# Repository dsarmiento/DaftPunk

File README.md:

# DaftPunk

##DaftController
DaftController will be the application that'll allow us to control our LED helmets via Bluetooth

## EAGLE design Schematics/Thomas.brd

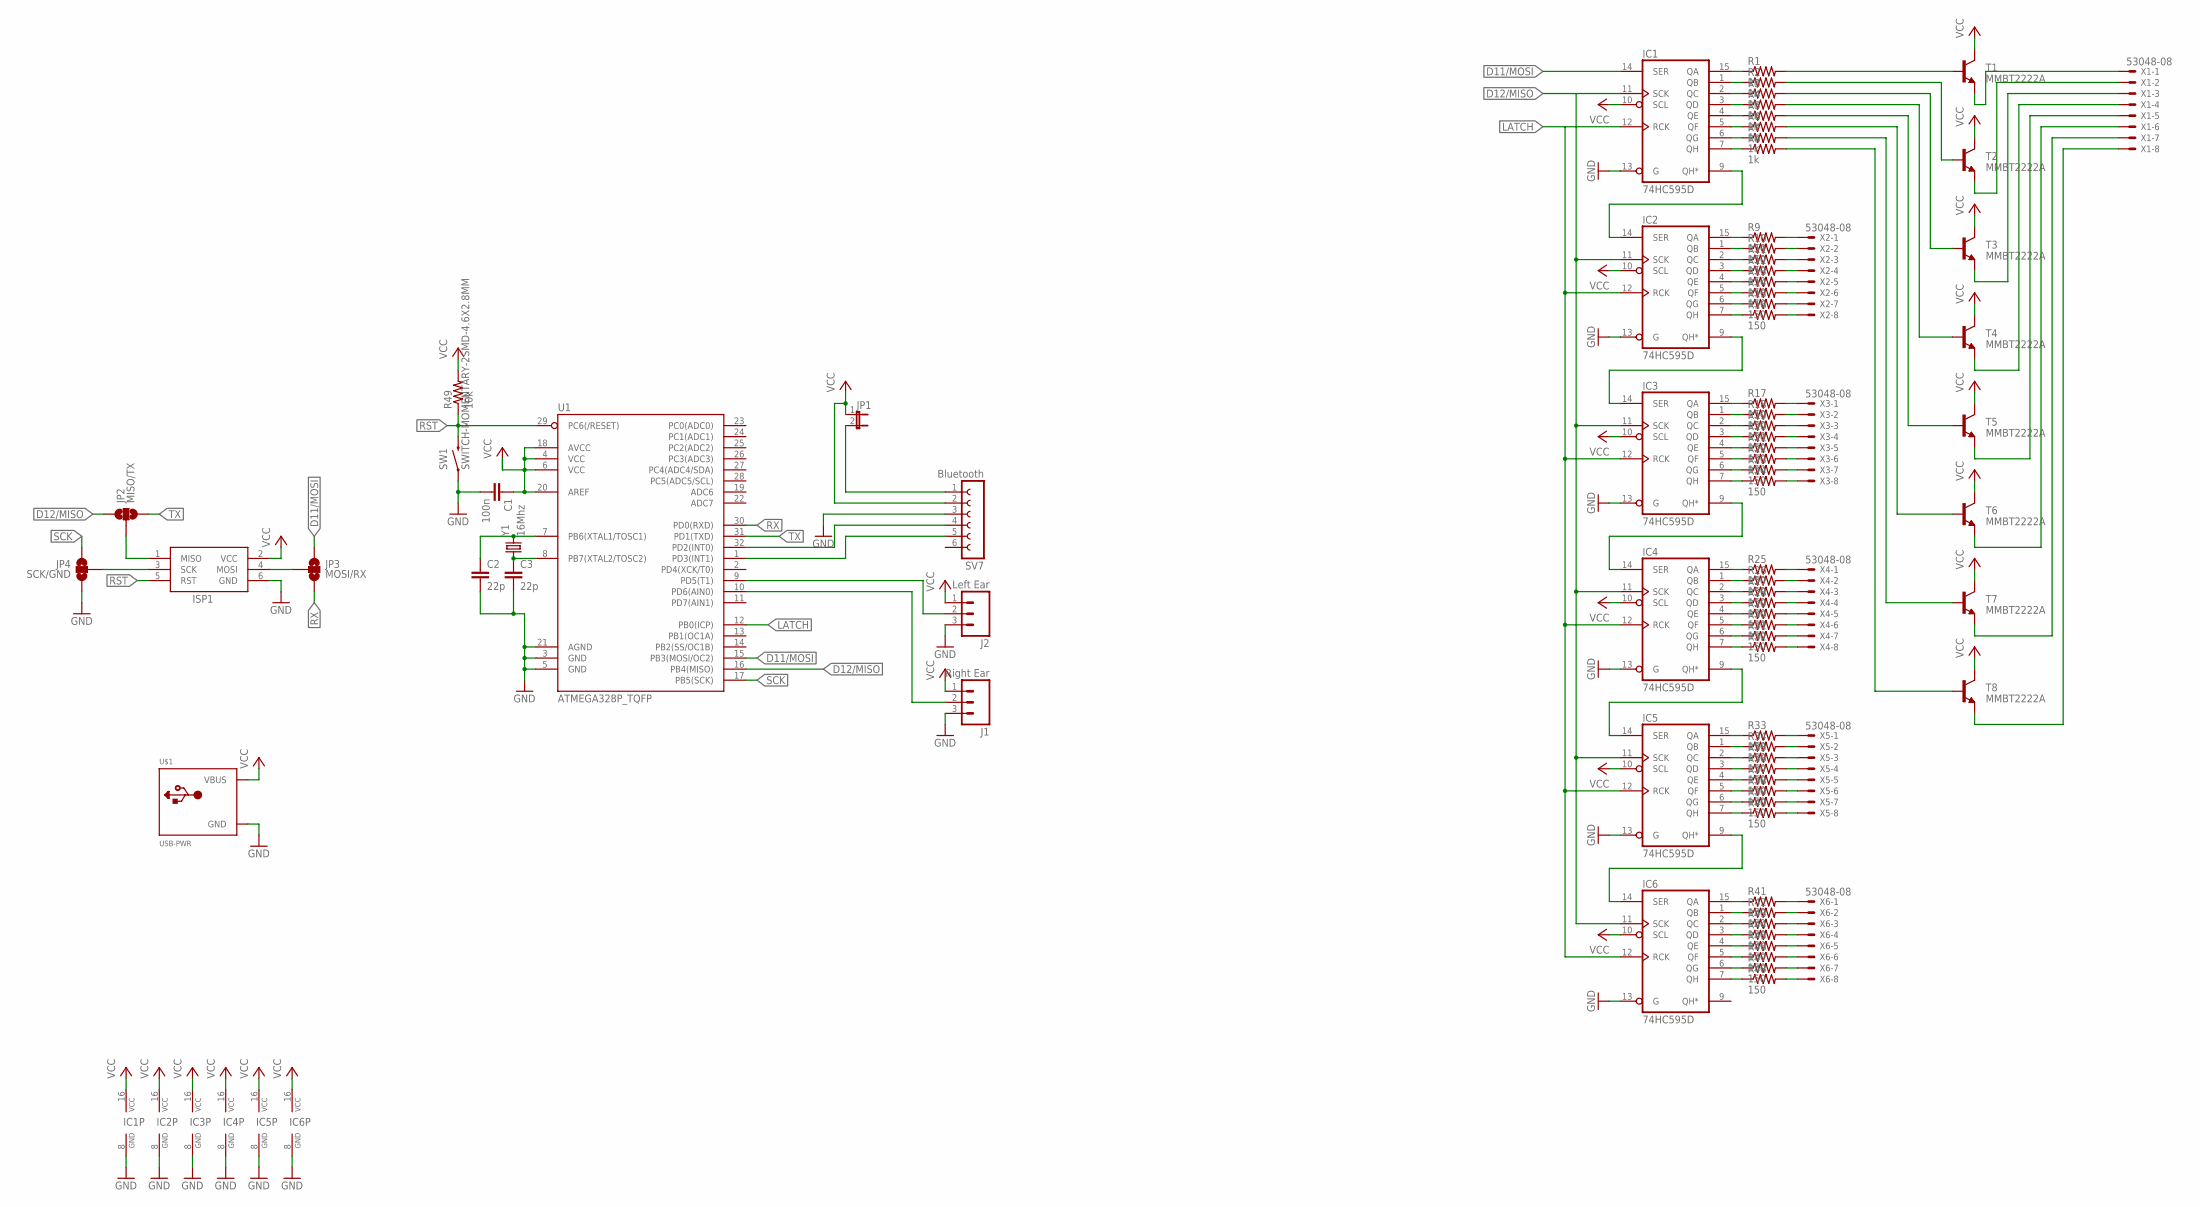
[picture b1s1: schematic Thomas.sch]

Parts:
C1: 100n; C0805K
C2, C3: 22p; C0805K
IC1, IC2, IC3, IC4, IC5, IC6: 74HC595D; SO16
ISP1: AVRISP-6; AVRISP
J1: Right Ear; 1X03
J2: Left Ear; 1X03
JP1: JUMPER-2SMD-NC; SJ_2S
JP2: MISO/TX; PAD-JUMPER-3-NO_YES_SILK
JP3: MOSI/RX; PAD-JUMPER-3-NO_YES_SILK
JP4: SCK/GND; PAD-JUMPER-3-NO_YES_SILK
R1, R2, R3, R4, R5, R6, R7, R8: 1k; R0805
R9, R10, R11, R12, R13, R14, R15, R16, R17, R18, R19, R20, R21, R22, R23, R24, R25, R26, R27, R28, R29, R30, R31, R32, R33, R34, R35, R36, R37, R38, R39, R40, R41, R42, R43, R44, R45, R46, R47, R48: 150; R0805
R49: 10k; R0805
SV7: Bluetooth; FE06
SW1: SWITCH-MOMENTARY-2SMD-4.6X2.8MM; TACTILE_SWITCH_SMD_4.6X2.8MM
T1, T2, T3, T4, T5, T6, T7, T8: MMBT2222A; SOT23-3
U1: ATMEGA328P_TQFP; TQFP32-08
U$1: USB-PWR; USB-MINIB-THM-MOLEX-PWRONLY
X1, X2, X3, X4, X5, X6: 53048-08
Y1: 16Mhz; CRYSTAL-SMD-3.2X1.5MM

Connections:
D11/MOSI: IC1.14 (SER), JP3.1, U1.15 (PB3(MOSI/OC2))
D12/MISO: IC1.11 (SCK), IC2.11 (SCK), IC3.11 (SCK), IC4.11 (SCK), IC5.11 (SCK), IC6.11 (SCK), JP2.1, U1.16 (PB4(MISO))
GND: C1.2, C2.2, C3.2, IC1.8 (GND), IC1.13 (G), IC2.8 (GND), IC2.13 (G), IC3.8 (GND), IC3.13 (G), IC4.8 (GND), IC4.13 (G), IC5.8 (GND), IC5.13 (G), IC6.8 (GND), IC6.13 (G), ISP1.6 (GND), J1.3, J2.3, JP4.3, SV7.3, SW1.1, SW1.2 (1), U1.3 (GND), U1.5 (GND), U1.21 (AGND), U$1.GND
LATCH: IC1.12 (RCK), IC2.12 (RCK), IC3.12 (RCK), IC4.12 (RCK), IC5.12 (RCK), IC6.12 (RCK), U1.12 (PB0(ICP))
unnamed: IC1.9 (QH*), IC2.14 (SER)
unnamed: IC2.9 (QH*), IC3.14 (SER)
unnamed: IC3.9 (QH*), IC4.14 (SER)
unnamed: IC4.9 (QH*), IC5.14 (SER)
unnamed: IC5.9 (QH*), IC6.14 (SER)
unnamed: R41.2, X6.1
unnamed: R42.2, X6.2
unnamed: R43.2, X6.3
unnamed: R44.2, X6.4
unnamed: R45.2, X6.5
unnamed: R46.2, X6.6
unnamed: R47.2, X6.7
unnamed: R48.2, X6.8
unnamed: R33.2, X5.1
unnamed: R34.2, X5.2
unnamed: R35.2, X5.3
unnamed: R36.2, X5.4
unnamed: R37.2, X5.5
unnamed: R38.2, X5.6
unnamed: R39.2, X5.7
unnamed: R40.2, X5.8
unnamed: R25.2, X4.1
unnamed: R26.2, X4.2
unnamed: R27.2, X4.3
unnamed: R28.2, X4.4
unnamed: R29.2, X4.5
unnamed: R30.2, X4.6
unnamed: R31.2, X4.7
unnamed: R32.2, X4.8
unnamed: R17.2, X3.1
unnamed: R18.2, X3.2
unnamed: R19.2, X3.3
unnamed: R20.2, X3.4
unnamed: R21.2, X3.5
unnamed: R22.2, X3.6
unnamed: R23.2, X3.7
unnamed: R24.2, X3.8
unnamed: R9.2, X2.1
unnamed: R10.2, X2.2
unnamed: R11.2, X2.3
unnamed: R12.2, X2.4
unnamed: R13.2, X2.5
unnamed: R14.2, X2.6
unnamed: R15.2, X2.7
unnamed: R16.2, X2.8
unnamed: JP1.2, SV7.1
unnamed: SV7.4, U1.32 (PD2(INT0))
unnamed: IC2.15 (QA), R9.1
unnamed: IC2.1 (QB), R10.1
unnamed: IC2.2 (QC), R11.1
unnamed: IC2.3 (QD), R12.1
unnamed: IC2.4 (QE), R13.1
unnamed: IC2.5 (QF), R14.1
unnamed: IC2.6 (QG), R15.1
unnamed: IC2.7 (QH), R16.1
unnamed: IC3.15 (QA), R17.1
unnamed: IC3.1 (QB), R18.1
unnamed: IC3.2 (QC), R19.1
unnamed: IC3.3 (QD), R20.1
unnamed: IC3.4 (QE), R21.1
unnamed: IC3.5 (QF), R22.1
unnamed: IC3.6 (QG), R23.1
unnamed: IC3.7 (QH), R24.1
unnamed: IC4.15 (QA), R25.1
unnamed: IC4.1 (QB), R26.1
unnamed: IC4.2 (QC), R27.1
unnamed: IC4.3 (QD), R28.1
unnamed: IC4.4 (QE), R29.1
unnamed: IC4.5 (QF), R30.1
unnamed: IC4.6 (QG), R31.1
unnamed: IC4.7 (QH), R32.1
unnamed: IC5.15 (QA), R33.1
unnamed: IC5.1 (QB), R34.1
unnamed: IC5.2 (QC), R35.1
unnamed: IC5.3 (QD), R36.1
unnamed: IC5.4 (QE), R37.1
unnamed: IC5.5 (QF), R38.1
unnamed: IC5.6 (QG), R39.1
unnamed: IC5.7 (QH), R40.1
unnamed: IC6.15 (QA), R41.1
unnamed: IC6.1 (QB), R42.1
unnamed: IC6.2 (QC), R43.1
unnamed: IC6.3 (QD), R44.1
unnamed: IC6.4 (QE), R45.1
unnamed: IC6.5 (QF), R46.1
unnamed: IC6.6 (QG), R47.1
unnamed: IC6.7 (QH), R48.1
unnamed: IC1.15 (QA), R1.1
unnamed: IC1.1 (QB), R2.1
unnamed: IC1.2 (QC), R3.1
unnamed: IC1.3 (QD), R4.1
unnamed: IC1.4 (QE), R5.1
unnamed: IC1.5 (QF), R6.1
unnamed: IC1.6 (QG), R7.1
unnamed: IC1.7 (QH), R8.1
unnamed: R1.2, T1.1 (B)
unnamed: R2.2, T2.1 (B)
unnamed: R3.2, T3.1 (B)
unnamed: R4.2, T4.1 (B)
unnamed: R5.2, T5.1 (B)
unnamed: R6.2, T6.1 (B)
unnamed: R7.2, T7.1 (B)
unnamed: R8.2, T8.1 (B)
unnamed: T1.2 (E), X1.1
unnamed: T2.2 (E), X1.2
unnamed: T3.2 (E), X1.3
unnamed: T4.2 (E), X1.4
unnamed: T5.2 (E), X1.5
unnamed: T6.2 (E), X1.6
unnamed: T7.2 (E), X1.7
unnamed: T8.2 (E), X1.8
unnamed: SV7.5, U1.1 (PD3(INT1))
unnamed: C2.1, U1.7 (PB6(XTAL1/TOSC1)), Y1.P$2 (2)
unnamed: C3.1, U1.8 (PB7(XTAL2/TOSC2)), Y1.P$1 (1)
unnamed: J2.2, U1.9 (PD5(T1))
unnamed: J1.2, U1.10 (PD6(AIN0))
unnamed: ISP1.1 (MISO), JP2.2
unnamed: ISP1.3 (SCK), JP4.2
unnamed: ISP1.4 (MOSI), JP3.2
RST: ISP1.5 (RST), R49.1, SW1.3 (2), SW1.4 (2), U1.29 (PC6(/RESET))
RX: JP3.3, U1.30 (PD0(RXD))
SCK: JP4.1, U1.17 (PB5(SCK))
TX: JP2.3, U1.31 (PD1(TXD))
VCC: C1.1, IC1.10 (SCL), IC1.16 (VCC), IC2.10 (SCL), IC2.16 (VCC), IC3.10 (SCL), IC3.16 (VCC), IC4.10 (SCL), IC4.16 (VCC), IC5.10 (SCL), IC5.16 (VCC), IC6.10 (SCL), IC6.16 (VCC), ISP1.2 (VCC), J1.1, J2.1, JP1.1, R49.2, SV7.2, T1.3 (C), T2.3 (C), T3.3 (C), T4.3 (C), T5.3 (C), T6.3 (C), T7.3 (C), T8.3 (C), U1.4 (VCC), U1.6 (VCC), U1.18 (AVCC), U1.20 (AREF), U$1.VBUS

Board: 2 copper layers, 84 parts (18 on the bottom side), 128 nets, no tracks yet.

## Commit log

2016-10-10 Readme
2016-10-10 RGB rotary encoder example
2016-10-12 LED_Matrix base with refactoring for this project
2016-10-14 New animations, tested on visor
2016-10-15 Added heart blink and eye blinking, not tested on visor
2016-10-16 Phone app and icon
2016-10-16 Restared with blank activity
2016-10-16 First toggle button!
2016-10-17 Multiple buttons, one active at a time
2016-10-17 Edited readme test push
2016-10-17 Theme colors
2016-10-17 added daftpunk image to readme
2016-10-17 still trying to add image...
2016-10-17 Project icon
2016-10-17 Added Icon image
2016-10-17 Renamed Matrix -> ThomasHelm
2016-10-18 Fixed eyes up and added all on/off
2016-10-18 more buttons and stuff
2016-10-18 Added buttons to LL, and made text not focus on startup
2016-10-18 Settings button
2016-10-18 Redid button layout to percentages, and added popup for bluetooth devices
2016-10-18 Bluetooth connects
2016-10-18 Animations now send
2016-10-19 more animations
2016-10-19 Forgot arduino bluetooth
2016-10-20 Refactoring arduino data array
2016-10-20 Arduino: ElIf to Switch, Android: Added DaftPunk
2016-10-20 Playing with whitespace
2016-10-20 Slider in android
2016-10-23 Added GuyManuelRGB code
2016-10-24 Fixed off by 1 error
2016-10-24 Added slider and speedup/down
2016-10-27 Added odd text for static text, attemping text from phone to arduino
2016-10-28 Minor changes
2016-10-28 Heart beat follow, pacman dot respawn, formatting
2016-10-29 added animations
2016-10-29 Added ear LED code
2016-11-25 Schematics and moving files

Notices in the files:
parts and their libraries:
SparkFun-DigitalIC: Licensing: Creative Commons ShareAlike 4.0 International - https://creativecommons.org/licenses/by-sa/4.0
